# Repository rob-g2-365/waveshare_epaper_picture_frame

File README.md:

# Waveshare Epaper Picture Frame

# Table of Contents
* [Introduction](#Introduction)
* [Knowledge Assumptions](#Knowledge-Assumptions)
* [File List](#File-List)
* [Specifications](#Specifications)
* [Parts List](#Parts-List)
* [Other Equipment Needed](#Other-Equipment-Needed)
* [Printing Instructions](#Printing-Instructions)
* [PCB Board Instructions](#PCB-Board-Instructions)
* [Assembly Instructions](#Assembly-Instructions)
* [Arduino Code ](#Arduino-Code)
* [Python Code](#Python-Code)
* [SD Card](#SD-Card)
* [Testing and Putting it Together](#Testing-and-Putting-it-Together)
* [Battery Life and Power Consumption](#Battery-Life-and-Power-Consumption)
* [Additional Resources](#Additional-Resources)

## Introduction

This project displays an image on an e-paper picture frame.  The picture switches once per day.  Included are the list of materials and how to build it.

## Knowledge Assumptions
I am assuming in this project that the user knows how to do the following:

* Read an electrical schematic.
* Basic soldering of through-hole components.
* Configure and build a project using the Arduino IDE.
* Slice a 3d Model and send it to a 3d printer.
* Put brass inserts into plastic using a soldering iron.
* Run a Python script.

## File List

* [Documentation](./docs)
* [Gerber files](./gerber)
* [STL Files](./stl)
* [Freecad code](./freecad)
* [Arduino IDE code](./arduino)
* [Convert Images Script](./convert_images)
* [Sample SD Card Image](./sdcard_image)
* [License file](.license)

## Specifications

* Display Size 5x7 inches or 10x18cm.
* Battery life should be about a year with alkaline batteries.

## Parts List

### Basic Parts
| Item           | Quantity  		 | Notes |
| :---           | :---     		 | :--- |
| PLA            | 400g      		 | Used just plain black PLA |
| Picture frame  | 1                 | [Used 5x7 Vertical Side Natural Frame by Threshold from Target](https://www.target.com/p/5--34--x-7--34--vertical-sides-natural-frame-antique-wood---threshold--8482-/-/A-54562757) |
| Solder         | Small Amount      |   |

### Fasteners

| Item           | Quantity  		 | Notes |
| :---           | :---     		 | :--- |
| M2 x 6mm Phillips Flat Countersunk Head Machine Screws	| 2 |  |
| M2.5 x 8mm Phillips flathead Machine Screws               | 2 |  |
| \#4 x 1/2 inch Wood Screws                                | 5 | Alternative use M3 x 15mm Woodscrews |
| M2.5 x 5mm Pan Phillips Cross Head Machine screws         | 12 |  You could just use the flathead screws for all screws M2.5 screws   |
| M2 x 4mm Brass Inserts	                                | 14 |    |
| M2.5 x 5.8mm Brass Inserts                                | 12 |  There is room for longer inserts. |

### Electrical Parts

Note that all electronic parts are through-hole components.  Note that many substitutes can be used for the resistors, capacitors, and diode.

| Item           									 | Part Number         																						| Quantity  |
| :---           									 | :---                     																				| :---      |
| Waveshare 7.3 inch ACeP 7-Color E-Paper 800x600    | [7.3 inch e-Paper Hat (F)](https://www.waveshare.com/product/displays/e-paper/7.3inch-e-paper-hat-f.htm) | 1         |
| MicroSD Card                                       | MicroSD Card                                                                                             | 1         |
| MicroSD Card Adapter for Arduino                   | [MicroSD Card Adapter](https://www.amazon.com/Storage-Memory-Shield-Module-Arduino/dp/B01IPCAP72)        | 1         |
| 3 AAA Battery Holder                               | [3 AAA Battery Holder](https://www.amazon.com/Velleman-BH431A-Battery-Holder-AAA-Cell/dp/B003TZDNN4)    | 1         |  
| ATmega328-P-PU Arduino Bootloader                  | [3647-ATMEGA328P-PUArduinoBootloader-ND](https://www.digikey.com/en/products/detail/universal-solder-electronics-ltd/ATMEGA328P-PU-Arduino-Bootloader/16822123)  | 1         | 
| 28 Pin DIP Socket                                  | [ICM-328-1-GT-HT](https://www.digikey.com/en/products/detail/adam-tech/ICM-328-1-GT-HT/9832998)          | 1         |
| PMOS - LP0701N3-G                                  | [LP0701N3-G-ND](https://www.digikey.com/en/products/detail/microchip-technology/LP0701N3-G/4902364)      | 1         |
| 22pF Capacitor                                     | [K220J15C0GF5TL2](https://www.digikey.com/en/products/detail/vishay-beyschlag-draloric-bc-components/K220J15C0GF5TL2/286459) | 2         |
| 100nF	Capacitor   							     | [K104K15X7RF5TL2](https://www.digikey.com/en/products/detail/vishay-beyschlag-draloric-bc-components/K104K15X7RF5TL2/286538) | 3         |
| Diode General Purpose                              | [BAW75-TAP](https://www.digikey.com/en/products/detail/vishay-general-semiconductor-diodes-division/BAW75-TAP/4825763)       | 1         |
| 10K Resistor                                       | [CF14JT10K0](https://www.digikey.com/en/products/detail/stackpole-electronics-inc/CF14JT10K0/1741265)    | 1         |
| 100K Resistor                                              | [CF14JT100K](https://www.digikey.com/en/products/detail/stackpole-electronics-inc/CF14JT100K/1741263)    | 2         |        
| SW_Push SWITCH TACTILE SPST                        | [B3F-1000](https://www.digikey.com/en/products/detail/omron-electronics-inc-emc-div/B3F-1000/33150)      | 1         | 
| 16Mhz 20pF Crystal                                 | [ECS-160-20-1X](https://www.digikey.com/en/products/detail/ecs-inc/ECS-160-20-1X/827525)                 | 1         |

We need a package of straight DuPont-style male row connectors in order to make the 1x2, 1x6, and 1x8 Connectors.  Also (10Cm) short multicolor Dupont Female to Female wires.

Note that the Micro SD Card doesn't need much capacity.  A 1Gb Micro SD Card should work.

## Other Equipment Needed

### Other Hardware Needed

* 3D Printer
* Soldering Iron
* [Arduino FTDI USB to Serial 5v Programmers](https://www.amazon.com/Serial-Adapter-Female-FT232RL-Windows/dp/B07RBK2P47) 

Also, it is a good idea to have troubleshooting equipment such as a multimeter and something to decode the SPI bus traffic.

### Software Needed

Need the software [Arduino IDE](https://www.arduino.cc/en/software) to build and download the code. I used version 2.1.0, but the latest version probably would work for you.

#### Arduino IDE Packages

| Package 														| Owner 			  | Current Version |
| :---    														| :---  			  | :---            |
| Arduino Builtin                                               | Arduino             | Built Into IDE  |
| [SD](https://www.arduino.cc/reference/en/libraries/sd/)      	| Arduino SparkFun    | 1.2.4           |
| [LowPower_LowPowerLab](https://www.arduino.cc/reference/en/libraries/lowpower_lowpowerlab/)  | LowerPowerLab       | 2.2 			|
| [EEPROM](https://docs.arduino.cc/learn/built-in-libraries/eeprom)	                           | Arduino                    | Built Into IDE  |
| [SPI](https://www.arduino.cc/reference/en/language/functions/communication/spi/)             | Arduino                    | Built Into IDE  |

### Python Environment

I used Python 3.9 with the Pillow (Python Image Library) 9.3.0 package installed.  The latest of each should work.

#### Optional Software

| Package 				| Version Used |
| :---    				| :---  	   |
| Freecad               | 0.21.2       |
| KiCad                 | 7.0          |

## Printing Instructions

### Printer Settings

| Settings  |  Used      |  Notes |
| :---      | :---       | :---   |
| Material  | PLA        |        |
| Nozzle    | 0.4mm      |        |
| Layer Height | 0.2mm   |        |
| Walls     | 5          | Needed for Brass Inserts |
| Infill    | 20%        |        |
| Supports  | Only Touching Build plate |   |

### 3D Printed Parts List

| Part          	|  Picture |
| :---          	| :---     |
| Main Part     	|  |
| Battery Cover 	|   |
| SD Card Cover 	|   |
| Display HAT Cover |    |
| Main Board Cover  |   | 
| Frame Border      |   |

## PCB Board Instructions

Gerber files are listed in the gerber directory.    I used OshPark to create the PCBs, but you should be able to use other vendors.

## Assembly Instructions

### Insert the M2.5 Brass Inserts into the Following Holes

Use a solder gun to insert the brass inserts.

### Insert the M2 Brass Inserts into the Following Holes

### Solder Components to PCB Board

Solder components to the PCB board.  The silkscreen shows the Component number location.

| Component Number | Part  |
| :---             | :---  |
| C1, C2           | 22pF  | 
| C3, C4, C5       | 100nF |
| D1               | General Purpose Diode |
| J1, J2           | Male Connector 01x06 Pin   |
| J3	           | Male Connector 01x08 Pin   |
| J4	           | Male Connector 01x02 Pin   |
| Q1	           | PMOS - LP0701N3-G |
| R1               | 10K Resistor |
| R2, R3	       | 100K Resistor |
| SW1              | Push button switch |
| U1	           | 28 Pin Connector for ATmega328-P |
| Y1	           | 16Mhz Crystal |

### Assemble the Main Part to Frame

Remove the original back assembly from the picture frame. We do not need the back of the picture frame, the screws, or the stand.  We only need the picture frame and the glass.

Mark Drill Holes.  (See frame back picture)
Drill holes into the picture frame using a 5/64 or 2mm drill bit.

Remove any stickers from the glass. Clean glass the glass using glass cleaner or isopropyl alcohol.   Ensure that no fingerprints are on the inside glass. 

Assemble in the following order:

1.  Wooden Frame
2.  Glass
3.  3D Printed Frame border
4.  E-paper display (Be sure the protective covering is removed and the e-paper display ribbon cable is at the top.)
5.  3D Printed Main Body

Use the #4 wood screw holes to attach the 3D Printed main body to the wooden picture frame.

### Put Boards into Main Picture Frame

### Connect the Ribbon Cable to the E-Hat

The extension cable for the e-paper display is not needed.   Connect the ribbon cable from the display to the e-hat.  Use M2 roundhead screws to attach the e-hat.

### Attach the Battery Case

Push battery wires through the holes in the main body.  Attach the battery case using M2 Flathead screws.

### Attach the Other Components to the Main Board

SD Card Adapter and Main Board used M2 Roundhead screws.  Be sure that the hole in the main body for the SD Card matches the SD Card slot.

Attach the main PCB board.  Ensure that the J3 screen is next to the hat connector and the SW1 is at the bottom of the display. 

### Make Connections to PCB Board

Attach the battery to J4.  PCB board is marked red for positive and black for negative.

Attach SD card connections to J2.  Chip select is closest to R1.  Please double-check [schematic](./docs/schematic.pdf).

Attach the Waveshare e-hat SPI connections to J3.  Gray should match GRY on the board.  Note that the BLK wire may be purple.

## Arduino Code 

### Arduino Code Overview

I had to make a couple of changes to the Waveshare drivers.  They are:

   A.  Changes with Waveshare drivers (SPI frequency and chips select)
   B.  Reduced the SPI clock speed.

### Download Instructions

Use Board type "Arduino Uno"

Attach FTDI USB to serial connector to J1 serial connector. 

### Enable Serial Debug

If you run into problems, you may want to enable serial debugging.  To enable serial debug out, uncomment line 50. 

<pre>
// Include this flag to turn on serial logging.
// #define SERIAL_DEBUG
</pre>

The last failure is saved in the EEPROM.  When booting, the error code is outputted over the serial port.   The error codes are listed in line 36 of debug.h.
<pre>
#define ERRORCODE_TEST                        0
#define ERRORCODE_EPAPER_INIT_FAILED          0x101
.
.
</pre>

## Python Code

### Preprocessing Portrait Images

Images that are formatted as portrait may need to be cropped so that faces and important details may be shown.

### Python Command-line Arguments

<pre>
	convert_images.py &lt;Source Directory&gt;  &lt;Destinations Directory&gt;
</pre>	
	
This command converts images from the source directory or its children into the destination directory.

Images in the destination directory are listed in the following order:  pic_000.bmp, pic_001.bmp, pic_002.bmp, etc.

This program also does the following:  

1.  Auto-adjusts the contrast.
2.  Increases the saturation so the images don't look washed out.
3.  Mirrors the image to looks correct when viewed from the picture frame.
4.  Crops the image so the image size is correct.
5.  Dithers the images so that only seven colors are needed to display the image.
6.  Randomizes the image's order.

## SD Card

### Sample SD Card Image

A sample SD Card image is located in:

### SD Card Format and Files

The Micro SD Card capacity can be small since the images don't occupy much space.  Format a Micro SD Card using Fat32.  Copy the processed image files to the root of the Micro SD Card.

Insert the Micro SD Card into the Micro SDCard Adapter for Arduino.

## Testing and Putting it Together

Verify that the image appears on the e-paper display.

Attach the 3D-printed covers.  

## Battery Life and Power Consumption

It takes about 134 seconds to change the image on the screen.  During this time, it uses approximately 40mA. 

$$ = 134 (seconds/switch) * 40 (mA) / 3600 (seconds/hour) $$

$$ = 1.5 (mAh/switch) $$

When idle, the current draw is about 10 uA.

$$ =  24 (hours) * 0.01 (mA) $$

$$ = 0.3 (mAh) $$

An approximate alkaline AAA battery life is about 1200mAh.  However, the picture frame cannot use the full capacity of the battery.  
Once the voltage goes below 3.8v, 1.25v per cell, the picture frame will stop working.  This is about 50% of the capacity.

Therefore, the battery life for the picture frame is:

$$ = 1200 mAh * 50% / 1.8 (mAh/ day) $$

$$ = 333 (days) $$

## Possible improvements.

### Use a ultra low I<sub>Q</sub> Boost Converter

An ultra-low I<sub>Q</sub> boost converter is one option for more battery life.  This will allow the battery pack voltage to be functional down 
to 2.7v, which is using the battery's full capacity. I don't know if using the full capacity of the battery will offset the leakage power lost through the boost converter.

## Additional Resources

[Waveshare 7.3inch e-Paper HAT (F) Manual](https://www.waveshare.com/wiki/7.3inch_e-Paper_HAT_(F))

[e Paper with Arduino and Raspberry Pi](https://www.youtube.com/watch?v=4onIqHClh2s&t=601s)

[Trolling My Mom With an E-Paper Picture](https://youtu.be/YawP9RjPcJA)

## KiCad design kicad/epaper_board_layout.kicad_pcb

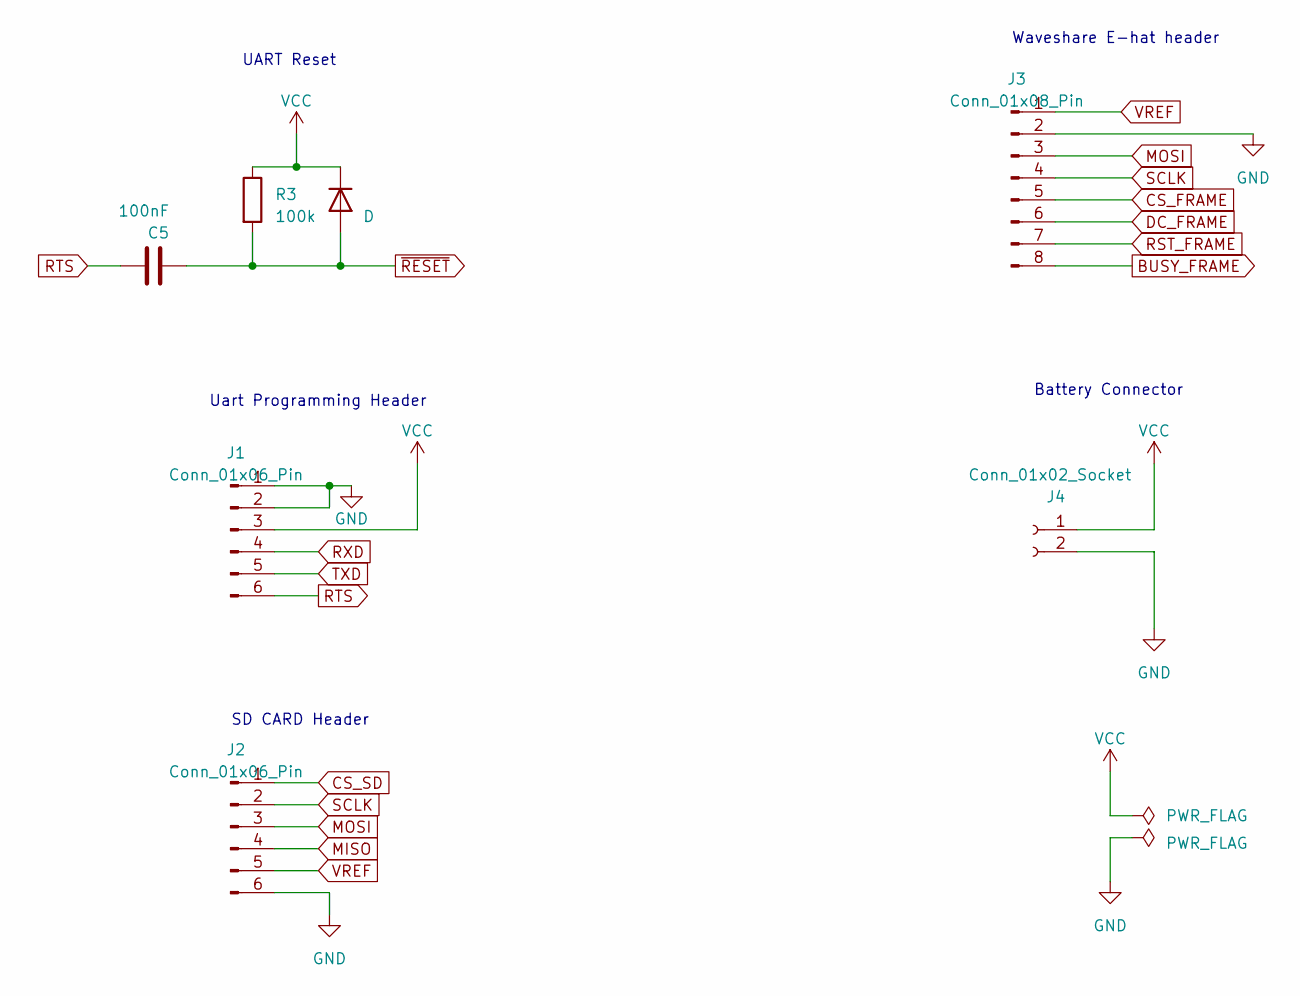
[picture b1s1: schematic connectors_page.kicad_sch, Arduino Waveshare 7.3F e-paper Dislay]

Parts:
C5: 100nF; C_Disc_D5.0mm_W2.5mm_P2.50mm
D1: D; D_DO-35_SOD27_P10.16mm_Horizontal
J1, J2: Conn_01x06_Pin; JST_EH_B6B-EH-A_1x06_P2.50mm_Vertical
J3: Conn_01x08_Pin; JST_EH_B8B-EH-A_1x08_P2.50mm_Vertical
J4: Conn_01x02_Socket; JST_EH_B2B-EH-A_1x02_P2.50mm_Vertical
R3: 100k; R_Axial_DIN0207_L6.3mm_D2.5mm_P10.16mm_Horizontal

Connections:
BUSY_FRAME: J3.8; also elsewhere on the board
CS_FRAME: J3.5; also elsewhere on the board
CS_SD: J2.1; also elsewhere on the board
DC_FRAME: J3.6; also elsewhere on the board
GND: J1.1, J1.2, J2.6, J3.2, J4.2; also elsewhere on the board
MISO: J2.4; also elsewhere on the board
MOSI: J2.3, J3.3; also elsewhere on the board
RST_FRAME: J3.7; also elsewhere on the board
RTS: C5.1, J1.6
RXD: J1.4; also elsewhere on the board
SCLK: J2.2, J3.4; also elsewhere on the board
TXD: J1.5; also elsewhere on the board
VCC: D1.1 (K), J1.3, J4.1, R3.1; also elsewhere on the board
VREF: J2.5, J3.1; also elsewhere on the board
~RESET: C5.2, D1.2 (A), R3.2; also elsewhere on the board

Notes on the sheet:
Waveshare E-hat header
SD CARD Header
Battery Connector
UART Reset
Uart Programming Header

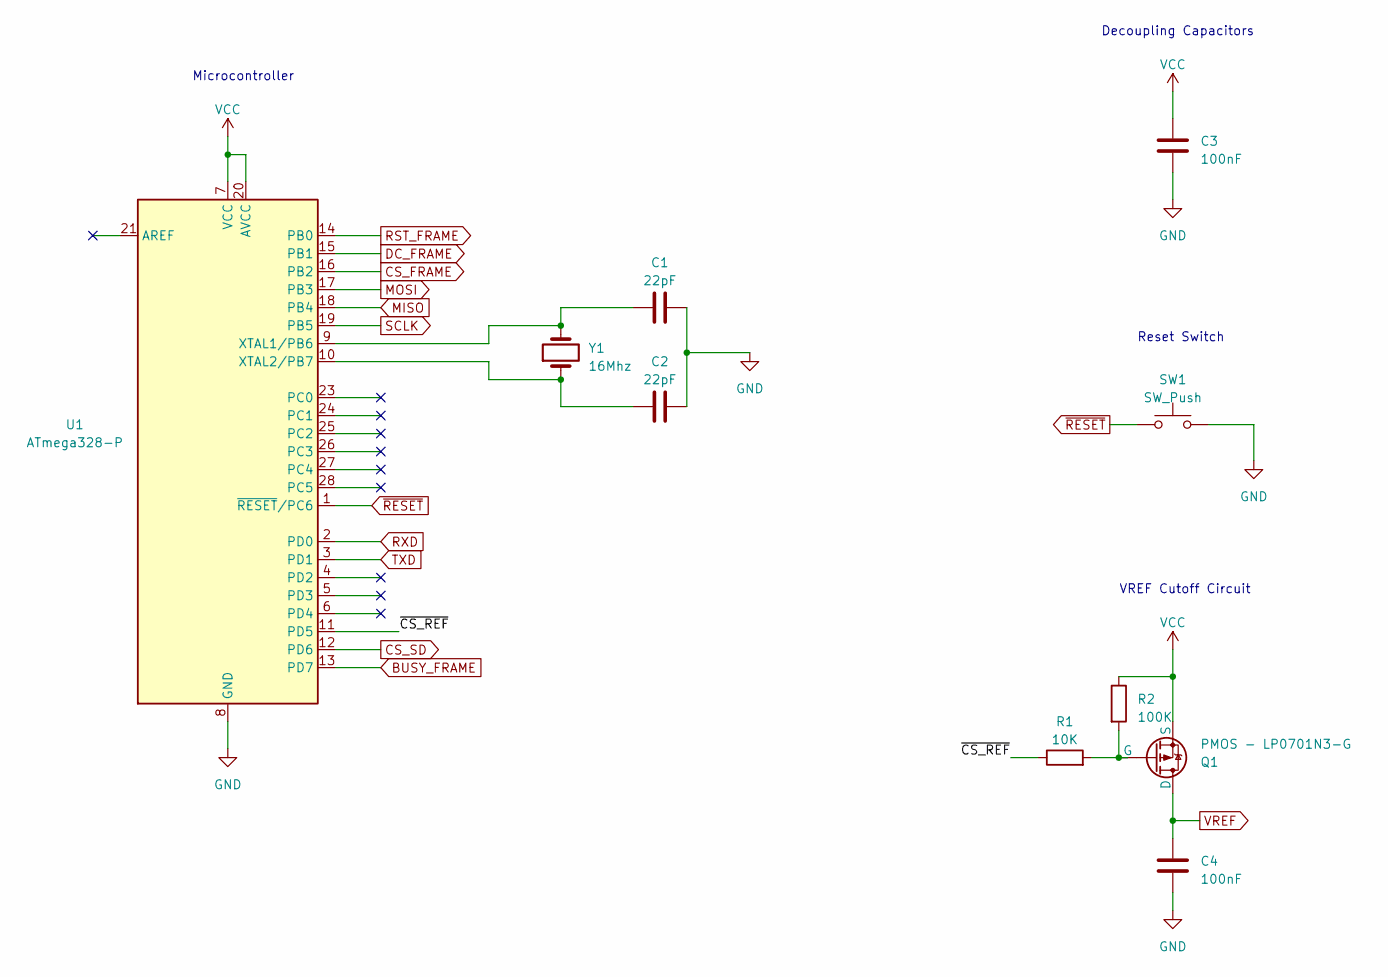
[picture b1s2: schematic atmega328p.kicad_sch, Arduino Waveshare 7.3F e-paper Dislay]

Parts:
C1, C2: 22pF; C_Disc_D5.0mm_W2.5mm_P2.50mm
C3, C4: 100nF; C_Disc_D5.0mm_W2.5mm_P2.50mm
Q1: PMOS - LP0701N3-G; TO-92
R1: 10K; R_Axial_DIN0207_L6.3mm_D2.5mm_P10.16mm_Horizontal
R2: 100K; R_Axial_DIN0207_L6.3mm_D2.5mm_P10.16mm_Horizontal
SW1: SW_Push; SW_PUSH_6mm_H5mm
U1: ATmega328-P; DIP-28_W7.62mm
Y1: 16Mhz; Crystal_HC49-4H_Vertical

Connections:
/atmega328p/~CS_REF: R1.1, U1.11 (PD5)
BUSY_FRAME: U1.13 (PD7); also elsewhere on the board
CS_FRAME: U1.16 (PB2); also elsewhere on the board
CS_SD: U1.12 (PD6); also elsewhere on the board
DC_FRAME: U1.15 (PB1); also elsewhere on the board
GND: C1.2, C2.2, C3.2, C4.2, SW1.2, U1.8 (GND), U1.22 (GND); also elsewhere on the board
MISO: U1.18 (PB4); also elsewhere on the board
MOSI: U1.17 (PB3); also elsewhere on the board
unnamed: Q1.2 (G), R1.2, R2.2
unnamed: C1.1, U1.9 (XTAL1/PB6), Y1.2
unnamed: C2.1, U1.10 (XTAL2/PB7), Y1.1
RST_FRAME: U1.14 (PB0); also elsewhere on the board
RXD: U1.2 (PD0); also elsewhere on the board
SCLK: U1.19 (PB5); also elsewhere on the board
TXD: U1.3 (PD1); also elsewhere on the board
VCC: C3.1, Q1.3 (S), R2.1, U1.7 (VCC), U1.20 (AVCC); also elsewhere on the board
VREF: C4.1, Q1.1 (D); also elsewhere on the board
~RESET: SW1.1, U1.1 (~RESET/PC6); also elsewhere on the board

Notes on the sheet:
Reset Switch
Microcontroller
Decoupling Capacitors
VREF Cutoff Circuit

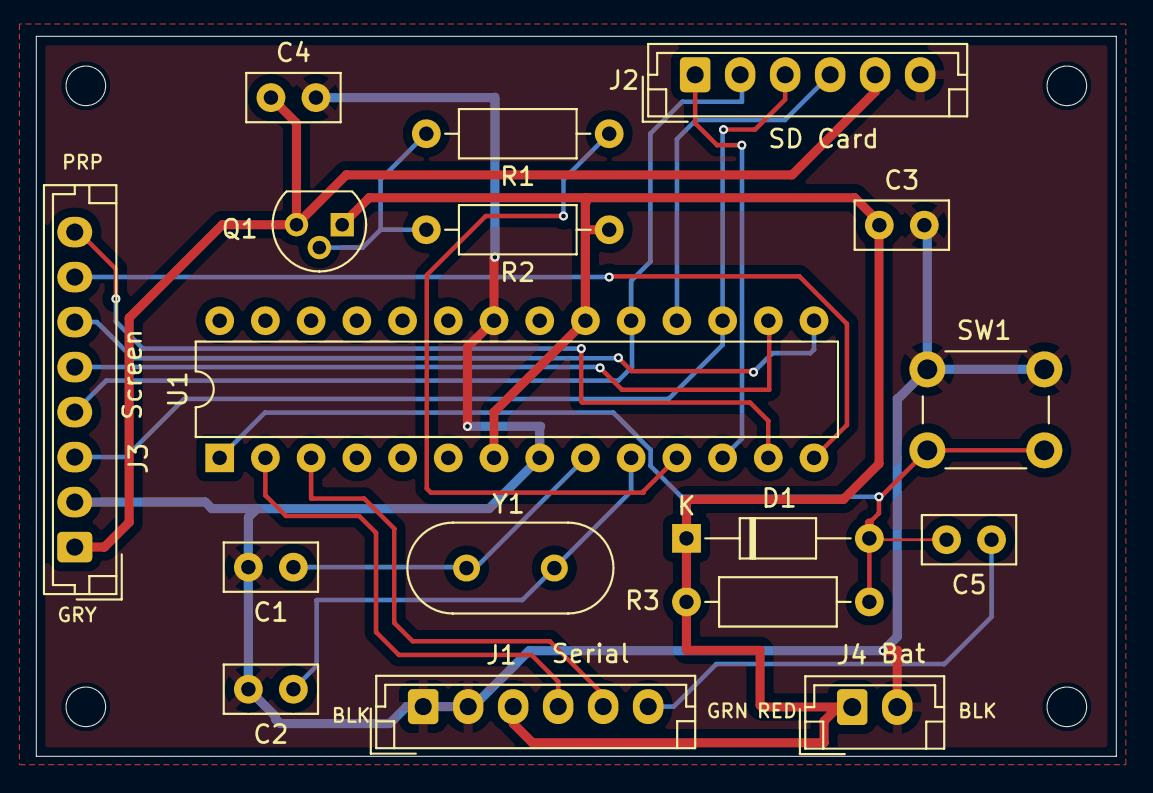
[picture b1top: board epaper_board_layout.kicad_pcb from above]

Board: 2 copper layers, 60.0 x 40.0 mm, 17 parts (0 on the bottom side), 19 nets.

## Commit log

2023-12-12 Added picture frame border stl
2023-12-12 Minor Documentation Changes
2023-12-12 Documentation Changes
2023-12-12 Minor documentation changes.
2023-12-12 Added addition resources section to documentation.
2023-12-13 Documentation changes.
2023-12-18 Added exif jpeg rotation to python script. Also removed duplicate python directories.
2023-12-19 Fixed capitolization of section headers.
2023-12-19 Added TOC.
2023-12-19 Minor doc change
2024-01-08 Moved arduino code to seperate epaper directory so that the Arduino IDE doesn't complain.
2024-01-09 Fixed problem where current was leaking through the MOSI and CS lines in the SD Card board.
2024-01-09 Added battery consumption information to documentation.
2024-01-09 Updating table of contents.
2024-01-09 Updated board schematic and layout because of FET labeled incorrectly in schematic.
2024-01-16 Changed code comments
2024-02-28 Testing out github actions. Plan to auto build on pushes.
2024-02-28 Previous version had a syntax error. Committing fix.
2024-02-28 Add check_run event.
2024-02-28 Testing real Arduino build script.
2024-02-28 Testing build action for ATMEGA328P
2024-02-28 Updated compile-sketches version.
2024-02-28 Added actions/setup-python for build action as suggested by error message.
2024-02-28 Try removing library version numbers.
2024-02-28 Try removing SPI library. May be built in.
2024-02-28 Try using eeprom version 2.0
2024-02-28 Try removing eeprom library.
2024-02-28 Adding Arduino_builtin library.
2024-02-28 Fix headerfile reference case for linux builds
2024-02-28 Fixing compiler warnings.
2024-02-28 Fixing actions issues.
2024-02-28 Removing arduino pro from being compiled.
2024-02-28 Remove unused parameter warning.
2024-02-29 Ran Readme.md through basic grammarly.
2024-02-29 Grammarly on README.md round 2.
2024-02-29 Found a couple mre README.md issues.
2024-02-29 Very minor documentation change.
2024-03-01 Added python tests cases
2024-03-01 Testing out running python in a github action.
2024-03-01 Try running python tests in a github action.
2024-03-01 Added installing the Pillow package when running unit tests.
2024-03-01 Exporting the PYTHONPATH variable when running unit tests.
2024-03-01 Fixing python unit tests when running github actions.
2024-03-01 Clean up unit tests.
2024-03-01 Change build action name.
2024-08-15 Added better error handling to display code.
2024-08-15 Ignoring python cache files.
2024-08-16 Fixed overflow problems with picture index.
2024-08-16 Added routine to clear eeprom data.
2024-08-17 Put the debug message strings in program memory.
2024-08-25 Changed powerup sequence.
2024-09-03 Change sleep loops to long
2024-09-03 Added the ability to produce test images for battery in testing.
2024-09-03 Changed saturation to 2.5 to brighten images.

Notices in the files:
kicad/atmega328p.kicad_sch:
creativecommons.org/licenses/by/4.0
License: CC BY 4.0
